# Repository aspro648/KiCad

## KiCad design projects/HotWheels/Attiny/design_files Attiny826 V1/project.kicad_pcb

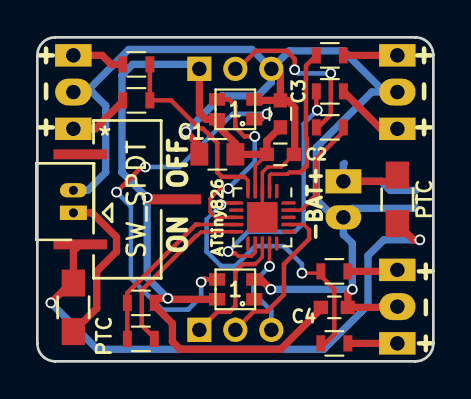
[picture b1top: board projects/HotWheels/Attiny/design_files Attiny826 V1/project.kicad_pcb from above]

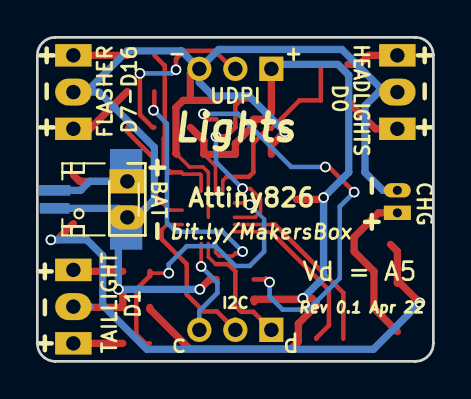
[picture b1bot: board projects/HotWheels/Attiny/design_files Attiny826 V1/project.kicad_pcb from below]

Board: 2 copper layers, 22.0 x 18.0 mm, 27 parts (4 on the bottom side), 24 nets.

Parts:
C1: 10uF; C_0805
C2: 0.1uF; C_0603
C3, C4: 1uF; C_0603
D0, D7: SK6812MINI; WS2812B-2020
F1, F2: PTC; R_0805_HandSoldering
J1: JST-SH; JST_SH_SM02B_hand_solder
J2: BAT; PIN_HEADER_LED
J3: CHG; Connector_Molex_PicoBlade_53047-0210
J4: UDPI; PinHeader_1x03_P2.00mm_Vertical
J5: HL; Pin_Header_THD_1x03
J6: TL; Pin_Header_THD_1x03
J7: FL; Pin_Header_THD_1x03
J8: I2C; PinHeader_1x03_P2.00mm_Vertical
R1: 1; R_0603
R2: 2; R_0603
R3, R4, R5, R6, R7, R10, R11: 100; R_0603
SW1: SW_SPDT; JS102011SCQN
U1: ATtiny826; VQFN-20-1EP_3x3mm_P0.4mm_EP1.7x1.7mm

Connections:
/D0: R3.1, R11.1, U1.5
/D1: R4.1, R5.1, U1.6
/D3: D0.3, U1.8
/D4: R1.2, R2.1, U1.9
/D5: R2.2, U1.10
/D7: R7.1, U1.12
/D12: J8.2, U1.17
/D16: R6.1, U1.2
/SCL: J8.3, U1.14
/SDA: J8.1, U1.13
/UPDI: R10.1, U1.19
GND: C1.2, C2.2, C3.2, C4.2, D0.2, D7.2, J1.1, J2.2, J3.2, J4.3, J5.2, J6.2, J7.2, U1.3, U1.21
unnamed: D0.1, D7.3
unnamed: F1.1, J3.1
unnamed: F1.2, F2.2, SW1.3
unnamed: F2.1, J1.2, J2.1
unnamed: J4.2, R10.2
unnamed: J5.1, R11.2
unnamed: J5.3, R3.2
unnamed: J6.1, R4.2
unnamed: J6.3, R5.2
unnamed: J7.1, R6.2
unnamed: J7.3, R7.2
VCC: C1.1, C2.1, C3.1, C4.1, D0.4, D7.4, J4.1, R1.1, SW1.2, U1.4

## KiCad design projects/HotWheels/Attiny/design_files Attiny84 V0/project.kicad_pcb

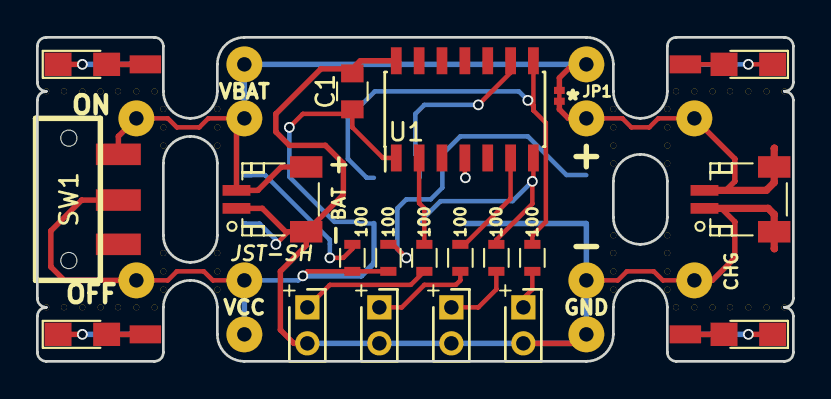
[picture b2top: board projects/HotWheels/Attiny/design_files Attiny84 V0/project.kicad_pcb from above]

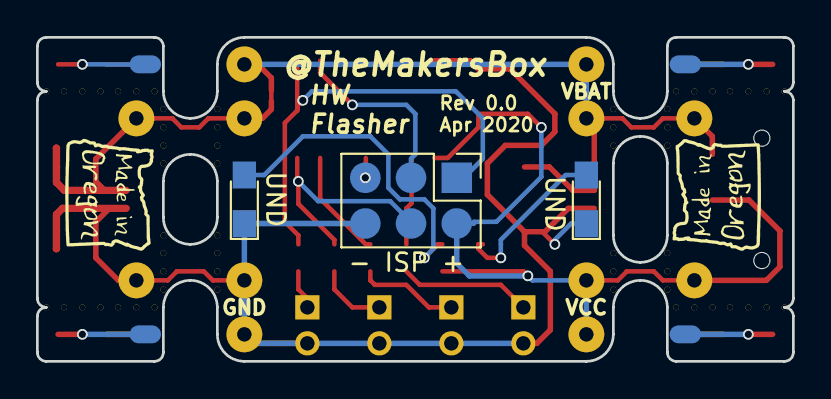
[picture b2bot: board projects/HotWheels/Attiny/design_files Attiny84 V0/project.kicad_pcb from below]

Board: 2 copper layers, 42.0 x 18.0 mm, 41 parts (3 on the bottom side), 23 nets.

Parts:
C1: 0.1uF; C_0805
CON1: AVR-ISP-6; Pin_Header_Straight_2x03_Pitch2.54mm
D4, D5: UND; LED_0805_HandSoldering
D20, D21, D22, D23: LED; LED_0805_HandSoldering
J1, J6, J7, J8: LED; PIN_HEADER_LED
J2: CHG; JST_SH_SM02B-SRSS-TB_02x1.00mm_Angled
J3: BAT; JST_SH_SM02B-SRSS-TB_02x1.00mm_Angled
J20, J21, J22, J23: LED; LED_PADS
J44, J45, J46, J47, J48, J49, J54, J55, J56, J57, J58, J59: Conn; SolderWirePad_single_0-8mmDrill
JP1: JMP; Jumper
R6, R7, R8, R9, R11, R12: 100; R_0603
SW1: SW_SPDT; SPST_SMD
U1: ATTINY84-20SSU; SOIC-14_3.9x8.7mm_Pitch1.27mm
VAL: MadeInOregonRev25
VAL#2: MadeInOregonRev25

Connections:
+BATT: J2.2, J3.2, J44.1, J46.1, J48.1, J54.1, J56.1, J58.1, JP1.1, JP1.2, SW1.1
/D5: CON1.1, R7.1, U1.8
/D6: CON1.4, R8.1, U1.7
/D7: R6.1, U1.6
/D8: R9.1, U1.2
/RESET: CON1.5, U1.4
/SCK: CON1.3, U1.9
GND: C1.2, CON1.6, D4.1, D5.1, J1.2, J2.1, J3.1, J6.2, J7.2, J8.2, J45.1, J47.1, J49.1, U1.14
unnamed: D4.2, R11.2
unnamed: D5.2, R12.2
unnamed: D20.1, J20.2
unnamed: D20.2, J20.1
unnamed: D21.1, J21.2
unnamed: D21.2, J21.1
unnamed: D22.1, J22.2
unnamed: D22.2, J22.1
unnamed: D23.1, J23.2
unnamed: D23.2, J23.1
unnamed: J1.1, R6.2
unnamed: J6.1, R7.2
unnamed: J7.1, R8.2
unnamed: J8.1, R9.2
VCC: C1.1, CON1.2, J55.1, J57.1, J59.1, R11.1, R12.1, SW1.2, U1.1

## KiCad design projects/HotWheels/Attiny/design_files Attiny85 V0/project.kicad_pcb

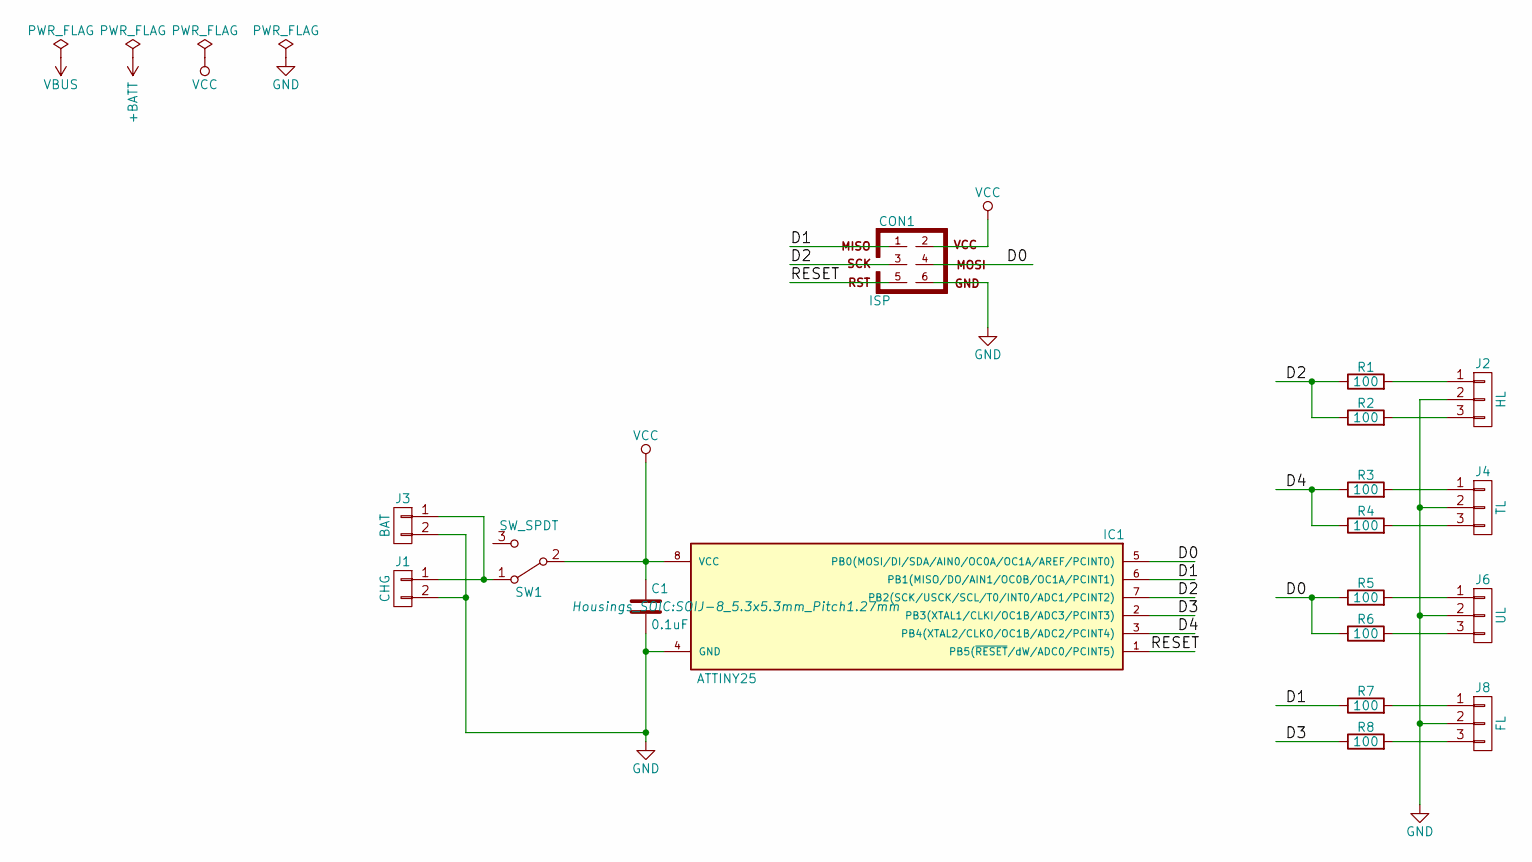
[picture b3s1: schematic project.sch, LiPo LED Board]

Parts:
C1: 0.1uF; C_0805
CON1: ISP; Pin_Header_Straight_2x03_Pitch2.54mm
IC1: ATTINY25; SOIJ-8_5.3x5.3mm_Pitch1.27mm
J1: CHG; Connector_Molex_PicoBlade_53047-0210
J2: HL; Pin_Header_SMD_1x03
J3: BAT; PIN_HEADER_LED
J4: TL; Pin_Header_SMD_1x03
J6: UL; Pin_Header_SMD_1x03
J8: FL; Pin_Header_SMD_1x03
R1: 100; R_0805_HandSoldering
R2, R3, R4, R5, R6, R7, R8: 100; R_0603
SW1: SW_SPDT; JS102011SCQN

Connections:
/D0: CON1.4, IC1.5 (PB0(MOSI/DI/SDA/AIN0/OC0A/OC1A/AREF/PCI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), R5.1, R6.1
/D1: CON1.1, IC1.6 (PB1(MISO/DO/AIN1/OC0B/OC1A/PCINT1)), R7.1
/D2: CON1.3, IC1.7 (PB2(SCK/USCK/SCL/T0/INT0/ADC1/PCINT2)), R1.1, R2.1
/D3: IC1.2 (PB3(XTAL1/CLKI/OC1B/ADC3/PCINT3)), R8.1
/D4: IC1.3 (PB4(XTAL2/CLKO/OC1B/ADC2/PCINT4)), R3.1, R4.1
/RESET: CON1.5, IC1.1 (PB5(~RESET~/dW/ADC0/PCINT5))
GND: C1.2, CON1.6, IC1.4 (GND), J1.2, J2.2, J3.2, J4.2, J6.2, J8.2
unnamed: J1.1, J3.1, SW1.1 (A)
unnamed: J2.1, R1.2
unnamed: J2.3, R2.2
unnamed: J4.1, R3.2
unnamed: J4.3, R4.2
unnamed: J6.1, R5.2
unnamed: J6.3, R6.2
unnamed: J8.1, R7.2
unnamed: J8.3, R8.2
VCC: C1.1, CON1.2, IC1.8 (VCC), SW1.2 (B)

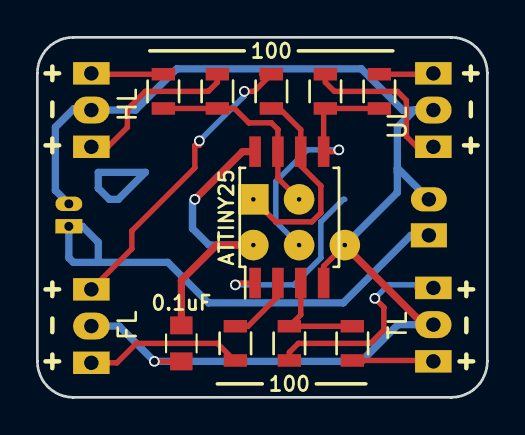
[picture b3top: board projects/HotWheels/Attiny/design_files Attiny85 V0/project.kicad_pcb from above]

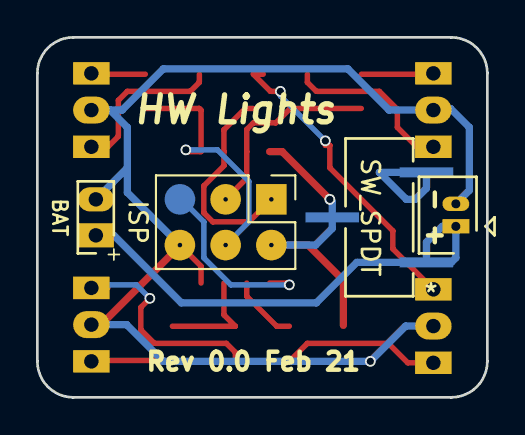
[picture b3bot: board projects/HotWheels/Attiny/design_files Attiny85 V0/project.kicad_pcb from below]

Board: 2 copper layers, 25.0 x 20.0 mm, 18 parts (4 on the bottom side), 17 nets.

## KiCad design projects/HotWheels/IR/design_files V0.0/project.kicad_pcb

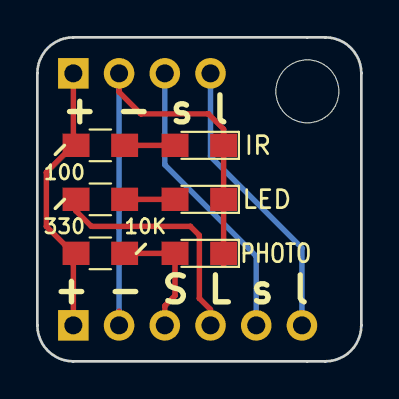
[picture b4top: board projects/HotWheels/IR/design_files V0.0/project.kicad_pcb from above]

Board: 2 copper layers, 18.0 x 18.0 mm, 8 parts (0 on the bottom side), 8 nets.

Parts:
D1: IR; LED_0805_HandSoldering
D2: LED; LED_0805_HandSoldering
J1: CONN_01X06; Pin_Header_Straight_1x06_Pitch2.54mm
J2: CONN_01X04; Pin_Header_Straight_1x04_Pitch2.54mm
Q1: PHOTO; LED_0805_HandSoldering
R1: 100; R_0805_HandSoldering
R2: 330; R_0805_HandSoldering
R3: 10K; R_0805_HandSoldering

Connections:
/GND: D1.1, D2.1, J1.2, J2.2, Q1.1
/LED1: J1.4, R2.2
/LED2: J1.5, J2.3
/SIG1: J1.3, Q1.2, R3.2
/SIG2: J1.6, J2.4
/VCC: J1.1, J2.1, R1.2, R3.1
unnamed: D1.2, R1.1
unnamed: D2.2, R2.1

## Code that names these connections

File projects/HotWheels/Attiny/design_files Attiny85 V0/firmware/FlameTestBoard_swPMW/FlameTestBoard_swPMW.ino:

/******************************************************************************
by Ken Olsen (648.ken@gmail.com) 
MakersBox.blogspot.com



Not all Attiny cores support the tone() function. Try this one
https://github.com/SpenceKonde/ATTinyCore

ATMEL ATTINY45/85 Pin Assignments
                   +-\/-+
  Ain0 (D 5) PB5  1|    |8  Vcc
  Ain3 (D 3) PB3  2|    |7  PB2 (D 2) Ain1
  Ain2 (D 4) PB4  3|    |6  PB1 (D 1) pwm1
             GND  4|    |5  PB0 (D 0) pwm0
   
******************************************************************************/


int HL = 2;   // headlights
int TL = 4;   // taillights
int FL1 = 1;  // flasher 1  PWM
int FL2 = 3;  // flasher 2
int UL = 0;   // Underlighting PWM
int pin = 2

#include "SoftPWM.h"

void setup()
{
  // Initialize
  SoftPWMBegin();

  // Create and set pin 13 to 0 (off)
  SoftPWMSet(pin, 0);

  // Set fade time for pin 13 to 100 ms fade-up time, and 500 ms fade-down time
  SoftPWMSetFadeTime(pin, 100, 500);
}

void loop()
{
  // Turn on - set to 100%
  SoftPWMSetPercent(pin, 100);

  // Wait for LED to turn on - you could do other tasks here
  delay(100);

  // Turn off - set to 0%
  SoftPWMSetPercent(pin, 0);

  // Wait for LED to turn off
  delay(500);
}

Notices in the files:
parts and their libraries:
Copyright 2016 Accelerated Designs. All rights reserved.
